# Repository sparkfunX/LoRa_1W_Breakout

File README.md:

SparkFun LoRa 1W Breakout
========================================

[*SparkFun LoRa 1W Breakout (SPX-18572)*](https://www.sparkfun.com/products/18572)

Do you need power? This breakout for the 915M30S module from EBYTE is a 1W (30dB) LoRa transceiver. LoRa is great for long range long range (miles), low power (in sleep), and low data rates (~500bps). This breakout board is designed to connect to any platform that has SPI and 6 available GPIO. We include a robust edge mount RP-SMA connector to connect large LoRa (915MHz) antennas. In addition, the on-board U.FL connector can be used if you need to get outside a metal enclosure. 

We've successfully broadcast 12 miles line-of-sight (thank you [foothills](https://www.google.com/search?q=boulder+foothills&tbm=isch)!) using this module but your results may vary.

Our example sketches make quick work of the initial setup for the [SX1276 LoRa transceiver](https://www.semtech.com/products/wireless-rf/lora-core/sx1276) from Semtech, and the RadioLib Arduino Library makes advanced configuration and [protocols](https://github.com/jgromes/RadioLib/wiki/Default-configuration#protocols) (AX.25, Hellschreiber, Morse, RTTY, and SSTV) a cinch too!

Repository Contents
-------------------

* **/Documents** - Datasheets and mechanical drawings
* **/Hardware** - All Eagle design files (.brd, .sch, .STL)

Product Versions
----------------

* [SPX-18572](https://www.sparkfun.com/products/18572)

License Information
-------------------

This product is _**open source**_! 

Please review the LICENSE.md file for license information. 

If you have any questions or concerns on licensing, please contact technical support on our [SparkFun forums](https://forum.sparkfun.com/viewforum.php?f=152).

Distributed as-is; no warranty is given.

- Your friends at SparkFun.

_<COLLABORATION CREDIT>_

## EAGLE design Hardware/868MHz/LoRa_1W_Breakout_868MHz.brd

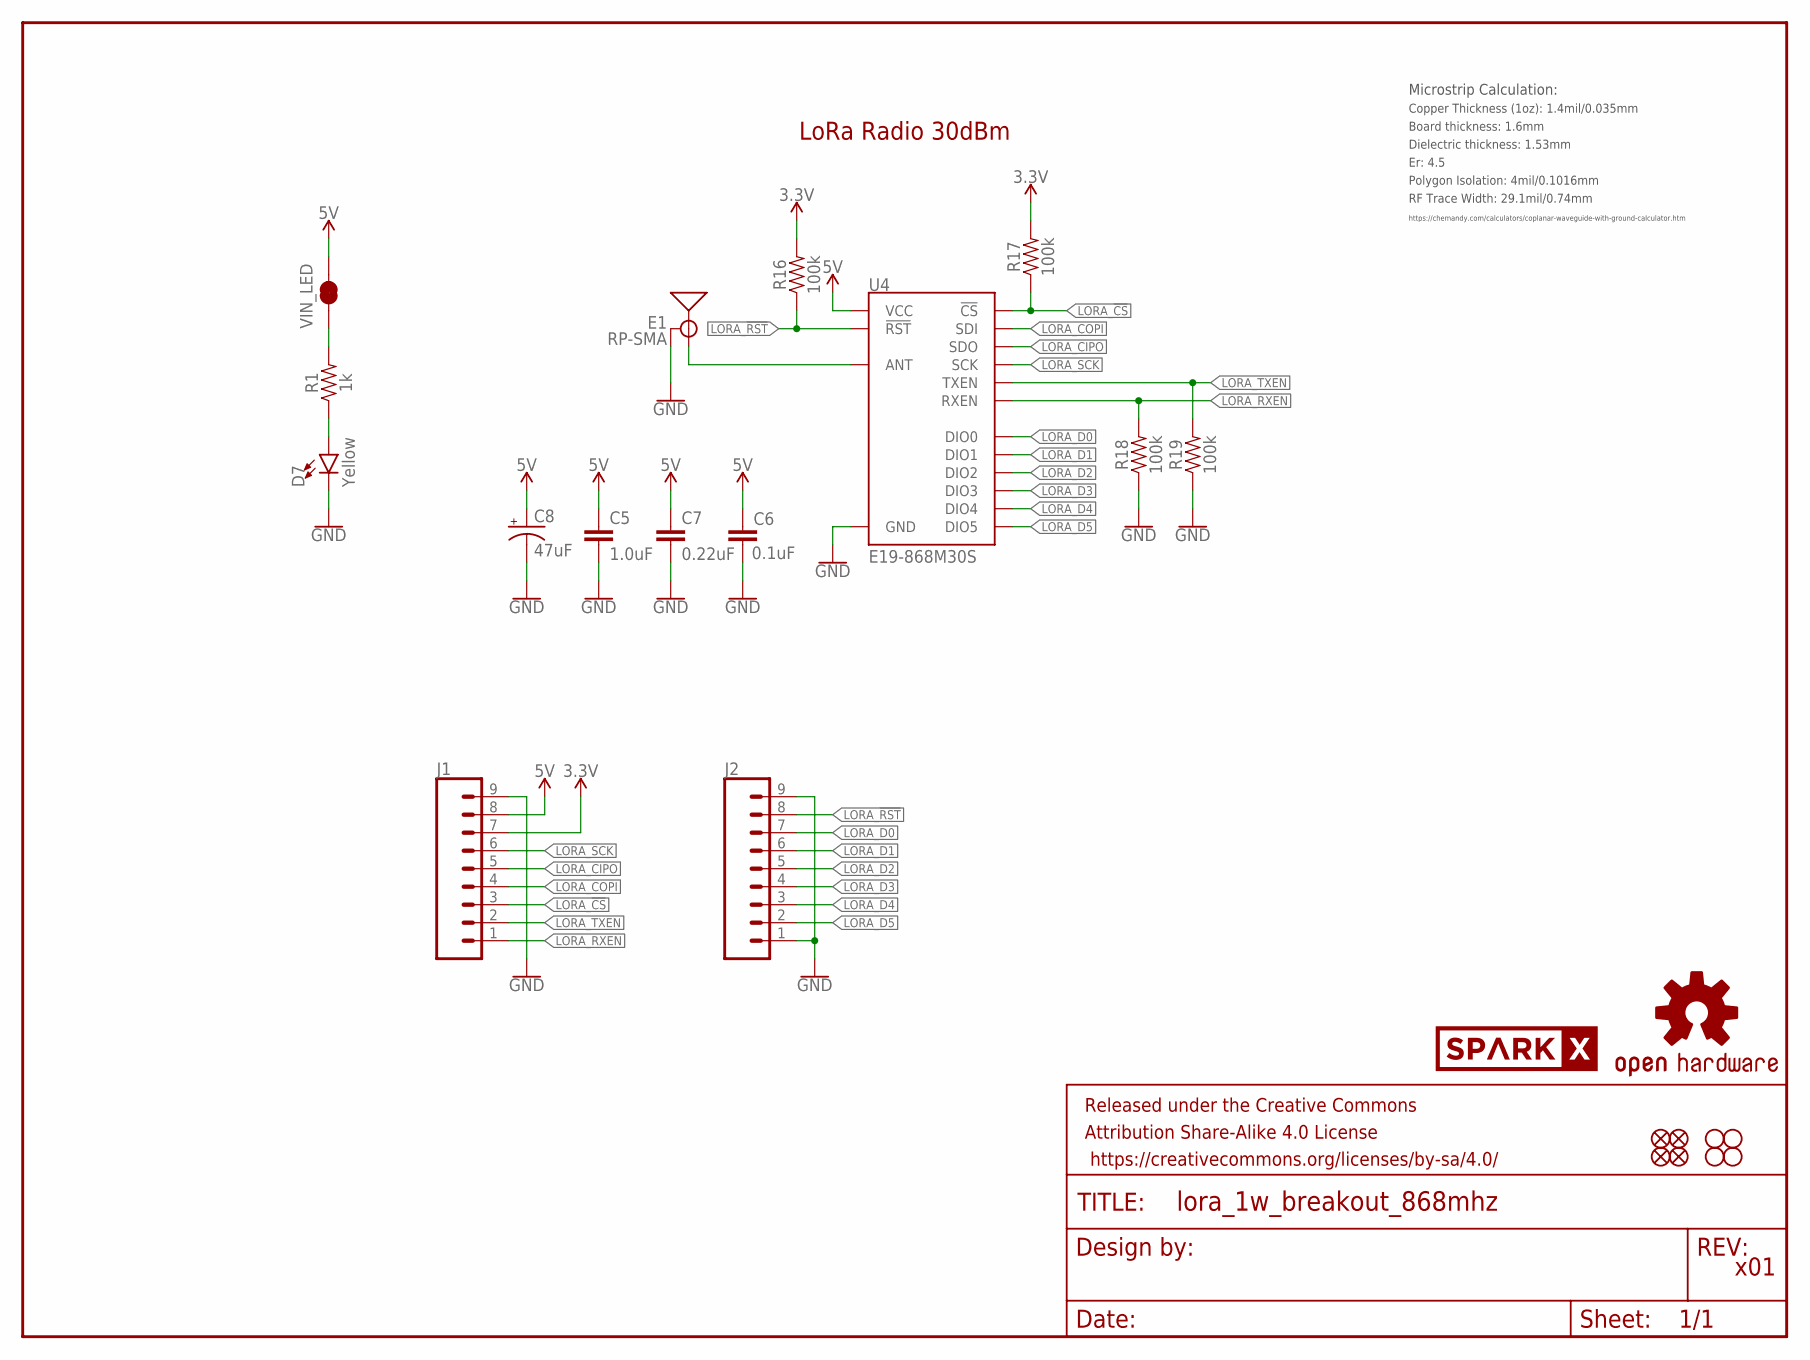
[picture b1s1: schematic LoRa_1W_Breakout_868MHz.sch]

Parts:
C5: 1.0uF; 0603
C6: 0.1uF; 0603
C7: 0.22uF; 0603
C8: 47uF; EIA3528
D7: Yellow; LED-0603
E1: RP-SMA; SMA-EDGE
FD1, FD2, FD3, FD4: FIDUCIALUFIDUCIAL; FIDUCIAL-MICRO
FRAME2: FRAME-LETTER; CREATIVE_COMMONS
H1, H2, H3, H4: STAND-OFF
J1, J2: CONN_09NO_SILK; 1X09_NO_SILK
LOGO3: OSHW-LOGOMINI; OSHW-LOGO-MINI
R1: 1k; 0603
R16, R17, R18, R19: 100k; 0603
U4: E19-868M30S; E19-915M30S
U$5: SPARKX-LOGO5; SPARKX-LARGE
VIN_LED: JUMPER-SMT_2_NC_TRACE_SILK; SMT-JUMPER_2_NC_TRACE_SILK

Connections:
3.3V: J1.7, R16.2, R17.2
5V: C5.1, C6.1, C7.1, C8.A (+), J1.8, U4.11 (VCC), VIN_LED.2
GND: C5.2, C6.2, C7.2, C8.C (-), D7.C, E1.GND@0 (GND), E1.GND@1 (GND), E1.GND@2 (GND), E1.GND@3 (GND), J1.9, J2.1, J2.9, R18.1, R19.1, U4.1 (GND), U4.9 (GND), U4.10 (GND), U4.18 (GND), U4.20 (GND), U4.21 (GND), U4.22 (GND)
LORA_!CS!: J1.3, R17.1, U4.15 (!CS)
LORA_!RST!: J2.8, R16.1, U4.8 (!RST)
LORA_CIPO: J1.5, U4.13 (SDO)
LORA_COPI: J1.4, U4.14 (SDI)
LORA_D0: J2.7, U4.7 (DIO0)
LORA_D1: J2.6, U4.6 (DIO1)
LORA_D2: J2.5, U4.5 (DIO2)
LORA_D3: J2.4, U4.4 (DIO3)
LORA_D4: J2.3, U4.3 (DIO4)
LORA_D5: J2.2, U4.2 (DIO5)
LORA_RF: E1.SIG (SIGNAL), U4.19 (ANT)
LORA_RXEN: J1.1, R18.2, U4.17 (RXEN)
LORA_SCK: J1.6, U4.12 (SCK)
LORA_TXEN: J1.2, R19.2, U4.16 (TXEN)
unnamed: R1.2, VIN_LED.1
unnamed: D7.A, R1.1

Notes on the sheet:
x01
LoRa Radio 30dBm
Board thickness: 1.6mm
Er: 4.5
Copper Thickness (1oz): 1.4mil/0.035mm
RF Trace Width: 29.1mil/0.74mm
Polygon Isolation: 4mil/0.1016mm
Dielectric thickness: 1.53mm
https://chemandy.com/calculators/coplanar-waveguide-with-ground-calculator.htm
Microstrip Calculation:

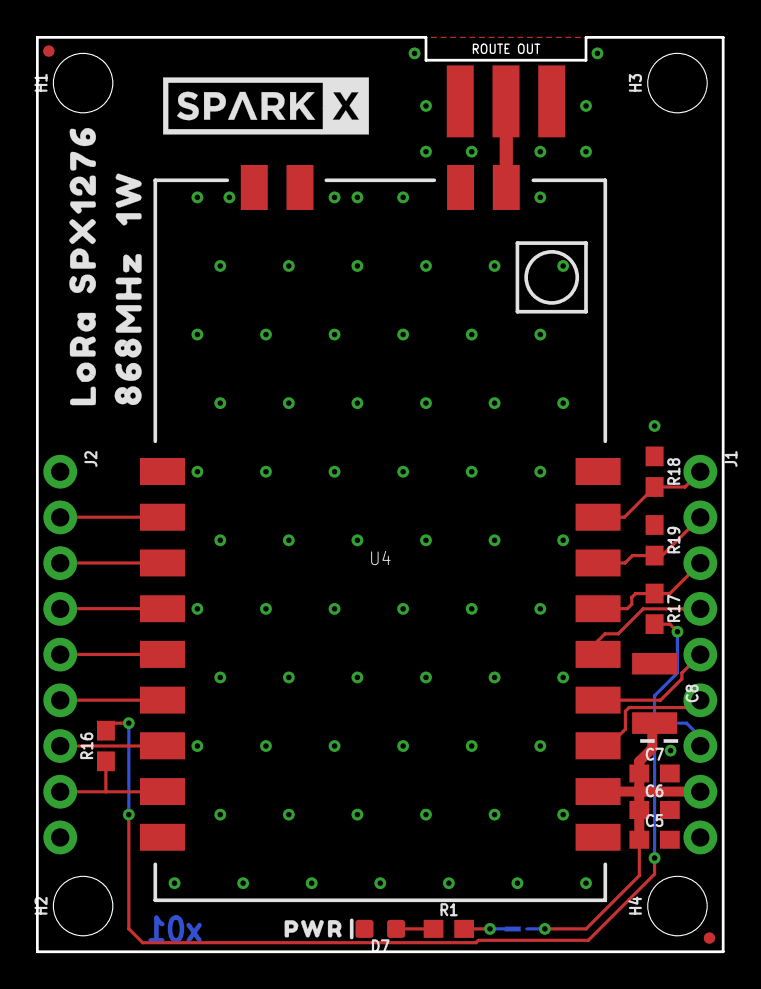
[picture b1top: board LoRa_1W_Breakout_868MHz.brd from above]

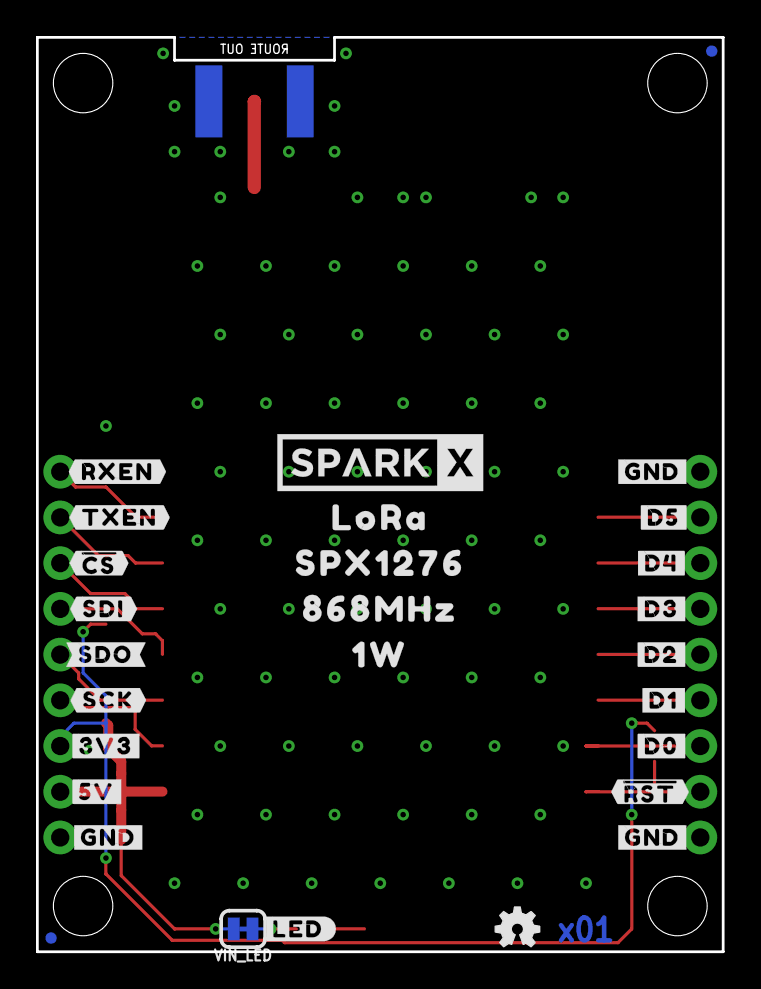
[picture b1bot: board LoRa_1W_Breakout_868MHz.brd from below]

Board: 2 copper layers, 38.1 x 50.8 mm, 55 parts (28 on the bottom side), 19 nets.

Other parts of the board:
U$1, U$67: LORA0
U$2, U$69: SPX12760
U$3, U$27: 1W1
U$4: PWR0
U$6: SPARKX-LOGO5; SPARKX-LARGE
U$7, U$9: 868MHZ0
U$15: #LED#0
U$43: #5V#1
U$44: #3V3#0
U$45: #SDO#3
U$46: #SDI#4
U$47: ##CS##5
U$48: #TXEN#6
U$49: #RXEN#7
U$52, U$53, U$61: #GND#8
U$54: #D5#6
U$55: #D4#5
U$56: #D3#4
U$57: #D2#3
U$58: #D1#2
U$59: #D0#1
U$60: ##RST##0
U$62: #SCK#2

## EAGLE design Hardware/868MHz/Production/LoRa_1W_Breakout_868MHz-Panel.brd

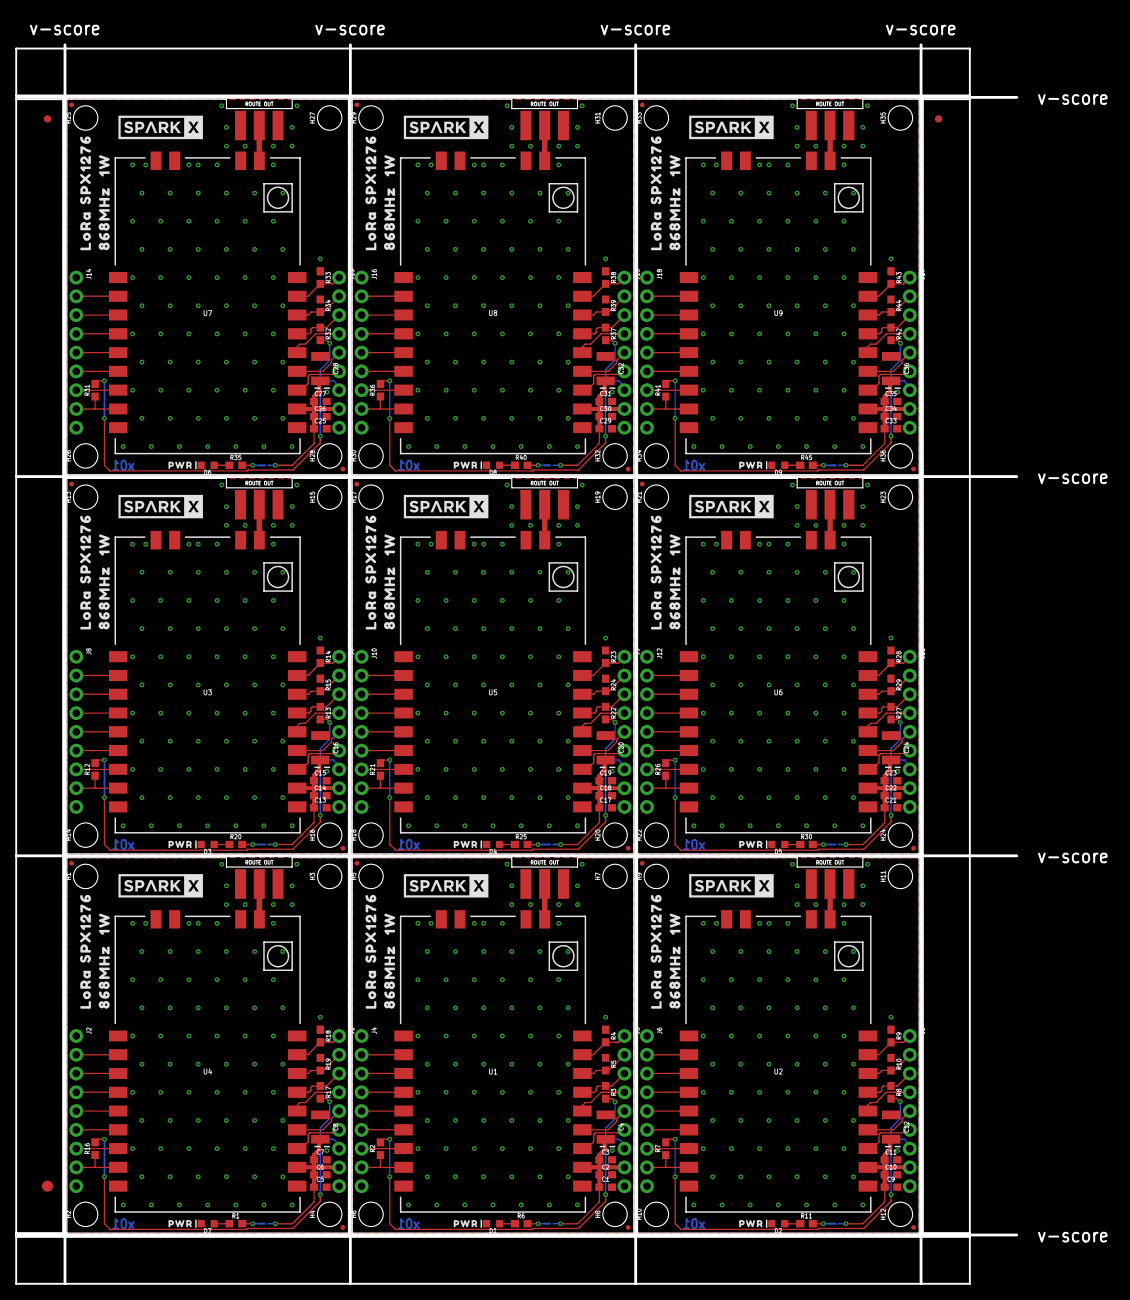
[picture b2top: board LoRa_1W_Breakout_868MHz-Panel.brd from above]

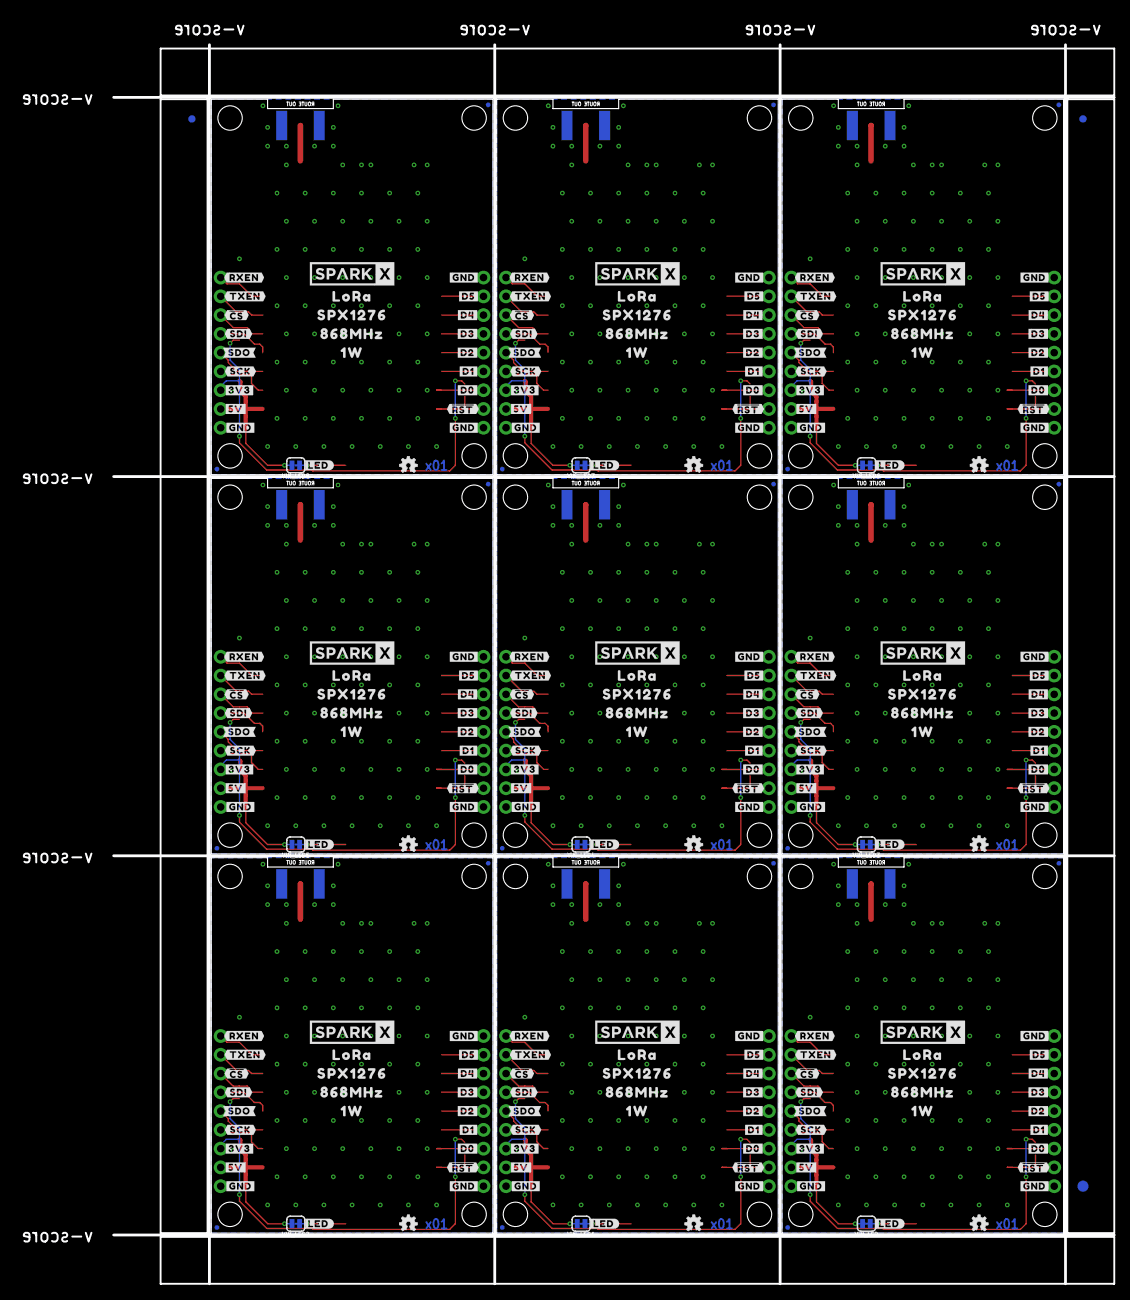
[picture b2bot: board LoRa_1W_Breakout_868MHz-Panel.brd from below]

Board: 2 copper layers, 135.4 x 167.6 mm, 492 parts (255 on the bottom side), 171 nets.

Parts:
C1, C5, C9, C13, C17, C21, C25, C29, C33: 1.0uF; 0603
C2, C6, C10, C14, C18, C22, C26, C30, C34: 0.1uF; 0603
C3, C7, C11, C15, C19, C23, C27, C31, C35: 0.22uF; 0603
C4, C8, C12, C16, C20, C24, C28, C32, C36: 47uF; EIA3528
D1, D2, D3, D4, D5, D6, D7, D8, D9: Yellow; LED-0603
E1, E2, E3, E4, E5, E6, E7, E8, E9: RP-SMA; SMA-EDGE
E$1, E$2, E$3, E$4: FIDUCIAL-1X2
E$5, E$6: FIDUCIAL-1.5X3
FD1, FD2, FD3, FD4, FD5, FD6, FD7, FD8, FD9, FD10, FD11, FD12, FD13, FD14, FD15, FD16, FD17, FD18, FD19, FD20, FD21, FD22, FD23, FD24, FD25, FD26, FD27, FD28, FD29, FD30, FD31, FD32, FD33, FD34, FD35, FD36: FIDUCIALUFIDUCIAL; FIDUCIAL-MICRO
H1, H2, H3, H4, H5, H6, H7, H8, H9, H10, H11, H12, H13, H14, H15, H16, H17, H18, H19, H20, H21, H22, H23, H24, H25, H26, H27, H28, H29, H30, H31, H32, H33, H34, H35, H36: STAND-OFF
J1, J2, J3, J4, J5, J6, J7, J8, J9, J10, J11, J12, J13, J14, J15, J16, J17, J18: 1X09_NO_SILK
LOGO1, LOGO2, LOGO3, LOGO4, LOGO5, LOGO6, LOGO7, LOGO8, LOGO9: OSHW-LOGOMINI; OSHW-LOGO-MINI
R1, R6, R11, R20, R25, R30, R35, R40, R45: 1k; 0603
R2, R3, R4, R5, R7, R8, R9, R10, R12, R13, R14, R15, R16, R17, R18, R19, R21, R22, R23, R24, R26, R27, R28, R29, R31, R32, R33, R34, R36, R37, R38, R39, R41, R42, R43, R44: 100k; 0603
U1, U2, U3, U4, U5, U6, U7, U8, U9: E19-915M30S
U$1, U$32, U$34, U$67, U$82, U$84, U$112, U$114, U$142, U$144, U$172, U$174, U$202, U$204, U$232, U$234, U$262, U$264: LORA0
U$2, U$33, U$35, U$69, U$83, U$85, U$113, U$115, U$143, U$145, U$173, U$175, U$203, U$205, U$233, U$235, U$263, U$265: SPX12760
U$3, U$27, U$31, U$36, U$81, U$86, U$111, U$116, U$141, U$146, U$171, U$176, U$201, U$206, U$231, U$236, U$261, U$266: 1W1
U$4, U$8, U$41, U$91, U$121, U$151, U$181, U$211, U$241: PWR0
U$5, U$6, U$37, U$38, U$87, U$88, U$117, U$118, U$147, U$148, U$177, U$178, U$207, U$208, U$237, U$238, U$267, U$268: SPARKX-LOGO5; SPARKX-LARGE
U$7, U$9, U$39, U$40, U$89, U$90, U$119, U$120, U$149, U$150, U$179, U$180, U$209, U$210, U$239, U$240, U$269, U$270: 868MHZ0
U$10, U$15, U$42, U$92, U$122, U$152, U$182, U$212, U$242: #LED#0
U$11, U$43, U$50, U$93, U$123, U$153, U$183, U$213, U$243: #5V#1
U$12, U$44, U$51, U$94, U$124, U$154, U$184, U$214, U$244: #3V3#0
U$13, U$45, U$63, U$95, U$125, U$155, U$185, U$215, U$245: #SDO#3
U$14, U$46, U$64, U$96, U$126, U$156, U$186, U$216, U$246: #SDI#4
U$16, U$47, U$65, U$97, U$127, U$157, U$187, U$217, U$247: ##CS##5
U$17, U$48, U$66, U$98, U$128, U$158, U$188, U$218, U$248: #TXEN#6
U$18, U$49, U$68, U$99, U$129, U$159, U$189, U$219, U$249: #RXEN#7
U$19, U$20, U$29, U$52, U$53, U$61, U$70, U$71, U$79, U$100, U$101, U$109, U$130, U$131, U$139, U$160, U$161, U$169, U$190, U$191, U$199, U$220, U$221, U$229, U$250, U$251, U$259: #GND#8
U$21, U$54, U$72, U$102, U$132, U$162, U$192, U$222, U$252: #D5#6
U$22, U$55, U$73, U$103, U$133, U$163, U$193, U$223, U$253: #D4#5
U$23, U$56, U$74, U$104, U$134, U$164, U$194, U$224, U$254: #D3#4
U$24, U$57, U$75, U$105, U$135, U$165, U$195, U$225, U$255: #D2#3
U$25, U$58, U$76, U$106, U$136, U$166, U$196, U$226, U$256: #D1#2
U$26, U$59, U$77, U$107, U$137, U$167, U$197, U$227, U$257: #D0#1
U$28, U$60, U$78, U$108, U$138, U$168, U$198, U$228, U$258: ##RST##0
U$30, U$62, U$80, U$110, U$140, U$170, U$200, U$230, U$260: #SCK#2
VIN_LED, VIN_LED1, VIN_LED2, VIN_LED3, VIN_LED4, VIN_LED5, VIN_LED6, VIN_LED7, VIN_LED8: JUMPER-SMT_2_NC_TRACE_SILK; SMT-JUMPER_2_NC_TRACE_SILK

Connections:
3.3V: J1.7, R16.2, R17.2
3.3V1: J3.7, R2.2, R3.2
3.3V2: J5.7, R7.2, R8.2
3.3V3: J7.7, R12.2, R13.2
3.3V4: J9.7, R21.2, R22.2
3.3V5: J11.7, R26.2, R27.2
3.3V6: J13.7, R31.2, R32.2
3.3V7: J15.7, R36.2, R37.2
3.3V8: J17.7, R41.2, R42.2
5V: C5.1, C6.1, C7.1, C8.A, J1.8, U4.11, VIN_LED.2
5V1: C1.1, C2.1, C3.1, C4.A, J3.8, U1.11, VIN_LED1.2
5V2: C9.1, C10.1, C11.1, C12.A, J5.8, U2.11, VIN_LED2.2
5V3: C13.1, C14.1, C15.1, C16.A, J7.8, U3.11, VIN_LED3.2
5V4: C17.1, C18.1, C19.1, C20.A, J9.8, U5.11, VIN_LED4.2
5V5: C21.1, C22.1, C23.1, C24.A, J11.8, U6.11, VIN_LED5.2
5V6: C25.1, C26.1, C27.1, C28.A, J13.8, U7.11, VIN_LED6.2
5V7: C29.1, C30.1, C31.1, C32.A, J15.8, U8.11, VIN_LED7.2
5V8: C33.1, C34.1, C35.1, C36.A, J17.8, U9.11, VIN_LED8.2
GND: C5.2, C6.2, C7.2, C8.C, D7.C, E1.GND@0, E1.GND@1, E1.GND@2, E1.GND@3, J1.9, J2.1, J2.9, R18.1, R19.1, U4.1, U4.9, U4.10, U4.18, U4.20, U4.21, U4.22
GND1: C1.2, C2.2, C3.2, C4.C, D1.C, E2.GND@0, E2.GND@1, E2.GND@2, E2.GND@3, J3.9, J4.1, J4.9, R4.1, R5.1, U1.1, U1.9, U1.10, U1.18, U1.20, U1.21, U1.22
GND2: C9.2, C10.2, C11.2, C12.C, D2.C, E3.GND@0, E3.GND@1, E3.GND@2, E3.GND@3, J5.9, J6.1, J6.9, R9.1, R10.1, U2.1, U2.9, U2.10, U2.18, U2.20, U2.21, U2.22
GND3: C13.2, C14.2, C15.2, C16.C, D3.C, E4.GND@0, E4.GND@1, E4.GND@2, E4.GND@3, J7.9, J8.1, J8.9, R14.1, R15.1, U3.1, U3.9, U3.10, U3.18, U3.20, U3.21, U3.22
GND4: C17.2, C18.2, C19.2, C20.C, D4.C, E5.GND@0, E5.GND@1, E5.GND@2, E5.GND@3, J9.9, J10.1, J10.9, R23.1, R24.1, U5.1, U5.9, U5.10, U5.18, U5.20, U5.21, U5.22
GND5: C21.2, C22.2, C23.2, C24.C, D5.C, E6.GND@0, E6.GND@1, E6.GND@2, E6.GND@3, J11.9, J12.1, J12.9, R28.1, R29.1, U6.1, U6.9, U6.10, U6.18, U6.20, U6.21, U6.22
GND6: C25.2, C26.2, C27.2, C28.C, D6.C, E7.GND@0, E7.GND@1, E7.GND@2, E7.GND@3, J13.9, J14.1, J14.9, R33.1, R34.1, U7.1, U7.9, U7.10, U7.18, U7.20, U7.21, U7.22
GND7: C29.2, C30.2, C31.2, C32.C, D8.C, E8.GND@0, E8.GND@1, E8.GND@2, E8.GND@3, J15.9, J16.1, J16.9, R38.1, R39.1, U8.1, U8.9, U8.10, U8.18, U8.20, U8.21, U8.22
GND8: C33.2, C34.2, C35.2, C36.C, D9.C, E9.GND@0, E9.GND@1, E9.GND@2, E9.GND@3, J17.9, J18.1, J18.9, R43.1, R44.1, U9.1, U9.9, U9.10, U9.18, U9.20, U9.21, U9.22
LORA_!CS!: J1.3, R17.1, U4.15
LORA_!CS!1: J3.3, R3.1, U1.15
LORA_!CS!2: J5.3, R8.1, U2.15
LORA_!CS!3: J7.3, R13.1, U3.15
LORA_!CS!4: J9.3, R22.1, U5.15
LORA_!CS!5: J11.3, R27.1, U6.15
LORA_!CS!6: J13.3, R32.1, U7.15
LORA_!CS!7: J15.3, R37.1, U8.15
LORA_!CS!8: J17.3, R42.1, U9.15
LORA_!RST!: J2.8, R16.1, U4.8
LORA_!RST!1: J4.8, R2.1, U1.8
LORA_!RST!2: J6.8, R7.1, U2.8
LORA_!RST!3: J8.8, R12.1, U3.8
LORA_!RST!4: J10.8, R21.1, U5.8
LORA_!RST!5: J12.8, R26.1, U6.8
LORA_!RST!6: J14.8, R31.1, U7.8
LORA_!RST!7: J16.8, R36.1, U8.8
LORA_!RST!8: J18.8, R41.1, U9.8
LORA_CIPO: J1.5, U4.13
LORA_CIPO1: J3.5, U1.13
LORA_CIPO2: J5.5, U2.13
LORA_CIPO3: J7.5, U3.13
LORA_CIPO4: J9.5, U5.13
LORA_CIPO5: J11.5, U6.13
LORA_CIPO6: J13.5, U7.13
LORA_CIPO7: J15.5, U8.13
LORA_CIPO8: J17.5, U9.13
LORA_COPI: J1.4, U4.14
LORA_COPI1: J3.4, U1.14
LORA_COPI2: J5.4, U2.14
LORA_COPI3: J7.4, U3.14
LORA_COPI4: J9.4, U5.14
LORA_COPI5: J11.4, U6.14
LORA_COPI6: J13.4, U7.14
LORA_COPI7: J15.4, U8.14
LORA_COPI8: J17.4, U9.14
LORA_D0: J2.7, U4.7
LORA_D1: J2.6, U4.6
LORA_D2: J2.5, U4.5
LORA_D3: J2.4, U4.4
LORA_D4: J2.3, U4.3
LORA_D5: J2.2, U4.2
LORA_D6: J4.7, U1.7
LORA_D7: J4.6, U1.6
LORA_D8: J4.5, U1.5
LORA_D9: J4.4, U1.4
LORA_D10: J4.3, U1.3
LORA_D11: J4.2, U1.2
LORA_D12: J6.7, U2.7
LORA_D13: J6.6, U2.6
LORA_D14: J6.5, U2.5
LORA_D15: J6.4, U2.4
LORA_D16: J6.3, U2.3
LORA_D17: J6.2, U2.2
LORA_D18: J8.7, U3.7
LORA_D19: J8.6, U3.6
LORA_D20: J8.5, U3.5
LORA_D21: J8.4, U3.4
LORA_D22: J8.3, U3.3
LORA_D23: J8.2, U3.2
LORA_D24: J10.7, U5.7
LORA_D25: J10.6, U5.6
LORA_D26: J10.5, U5.5
LORA_D27: J10.4, U5.4
LORA_D28: J10.3, U5.3
LORA_D29: J10.2, U5.2
LORA_D30: J12.7, U6.7
LORA_D31: J12.6, U6.6
LORA_D32: J12.5, U6.5
LORA_D33: J12.4, U6.4
LORA_D34: J12.3, U6.3
LORA_D35: J12.2, U6.2
LORA_D36: J14.7, U7.7
LORA_D37: J14.6, U7.6
LORA_D38: J14.5, U7.5
LORA_D39: J14.4, U7.4
LORA_D40: J14.3, U7.3
LORA_D41: J14.2, U7.2
LORA_D42: J16.7, U8.7
LORA_D43: J16.6, U8.6
LORA_D44: J16.5, U8.5
LORA_D45: J16.4, U8.4
LORA_D46: J16.3, U8.3
LORA_D47: J16.2, U8.2
LORA_D48: J18.7, U9.7
LORA_D49: J18.6, U9.6
LORA_D50: J18.5, U9.5
LORA_D51: J18.4, U9.4
LORA_D52: J18.3, U9.3
LORA_D53: J18.2, U9.2
LORA_RF: E1.SIG, U4.19
LORA_RF1: E2.SIG, U1.19
LORA_RF2: E3.SIG, U2.19
LORA_RF3: E4.SIG, U3.19
LORA_RF4: E5.SIG, U5.19
LORA_RF5: E6.SIG, U6.19
LORA_RF6: E7.SIG, U7.19
LORA_RF7: E8.SIG, U8.19
LORA_RF8: E9.SIG, U9.19
LORA_RXEN: J1.1, R18.2, U4.17
LORA_RXEN1: J3.1, R4.2, U1.17
LORA_RXEN2: J5.1, R9.2, U2.17
LORA_RXEN3: J7.1, R14.2, U3.17
LORA_RXEN4: J9.1, R23.2, U5.17
LORA_RXEN5: J11.1, R28.2, U6.17
LORA_RXEN6: J13.1, R33.2, U7.17
LORA_RXEN7: J15.1, R38.2, U8.17
LORA_RXEN8: J17.1, R43.2, U9.17
LORA_SCK: J1.6, U4.12
LORA_SCK1: J3.6, U1.12
LORA_SCK2: J5.6, U2.12
LORA_SCK3: J7.6, U3.12
LORA_SCK4: J9.6, U5.12
LORA_SCK5: J11.6, U6.12
LORA_SCK6: J13.6, U7.12
LORA_SCK7: J15.6, U8.12
LORA_SCK8: J17.6, U9.12
LORA_TXEN: J1.2, R19.2, U4.16
LORA_TXEN1: J3.2, R5.2, U1.16
LORA_TXEN2: J5.2, R10.2, U2.16
LORA_TXEN3: J7.2, R15.2, U3.16
LORA_TXEN4: J9.2, R24.2, U5.16
LORA_TXEN5: J11.2, R29.2, U6.16
LORA_TXEN6: J13.2, R34.2, U7.16
LORA_TXEN7: J15.2, R39.2, U8.16
LORA_TXEN8: J17.2, R44.2, U9.16
unnamed: R6.2, VIN_LED1.1
unnamed: D1.A, R6.1
unnamed: R11.2, VIN_LED2.1
unnamed: D2.A, R11.1
unnamed: R20.2, VIN_LED3.1
unnamed: D3.A, R20.1
unnamed: R25.2, VIN_LED4.1
unnamed: R1.2, VIN_LED.1
unnamed: D7.A, R1.1
unnamed: D4.A, R25.1
unnamed: R30.2, VIN_LED5.1
unnamed: D5.A, R30.1
unnamed: R35.2, VIN_LED6.1
unnamed: D6.A, R35.1
unnamed: R40.2, VIN_LED7.1
unnamed: D8.A, R40.1
unnamed: R45.2, VIN_LED8.1
unnamed: D9.A, R45.1

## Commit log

2021-09-03 Update to x02
2021-09-22 Remove backup files
2021-09-22 Add readme and license
2023-12-07 Add 433 and 868
2023-12-07 Add 868 manual
2023-12-07 Update schematics

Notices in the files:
parts and their libraries:
SparkFun-Aesthetics: Licensing: Creative Commons ShareAlike 4.0 International - https://creativecommons.org/licenses/by-sa/4.0
SparkFun-Aesthetics: Released under the Creative Commons Attribution Share-Alike 4.0 License
SparkFun-Aesthetics: https://creativecommons.org/licenses/by-sa/4.0
